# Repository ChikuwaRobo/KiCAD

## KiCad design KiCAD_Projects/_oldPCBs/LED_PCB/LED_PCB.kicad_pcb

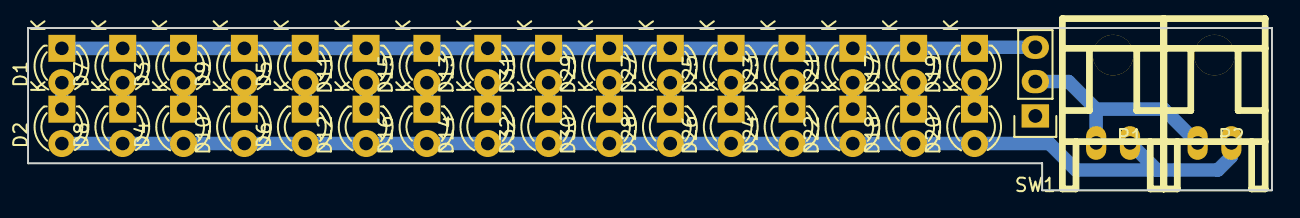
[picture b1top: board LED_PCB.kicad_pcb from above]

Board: 2 copper layers, 92.0 x 12.0 mm, 35 parts (0 on the bottom side), 19 nets.

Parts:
D1, D2, D3, D4, D5, D6, D7, D8, D9, D10, D11, D12, D13, D14, D15, D16, D17, D18, D19, D20, D21, D22, D23, D24, D25, D26, D27, D28, D29, D30, D31, D32: LED; LED-3MM
P1, P2: CONN_01X02; XA_2LC
SW1: SWITCH_INV; Pin_Header_Straight_1x03

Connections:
+BATT: P1.2, P2.2, SW1.2
GND: D2.2, D4.2, D6.2, D8.2, D10.2, D12.2, D14.2, D16.2, D18.2, D20.2, D22.2, D24.2, D26.2, D28.2, D30.2, D32.2, P1.1, P2.1
unnamed: D1.1, D3.1, D5.1, D7.1, D9.1, D11.1, D13.1, D15.1, D17.1, D19.1, D21.1, D23.1, D25.1, D27.1, D29.1, D31.1, SW1.3
unnamed: D1.2, D2.1
unnamed: D3.2, D4.1
unnamed: D5.2, D6.1
unnamed: D7.2, D8.1
unnamed: D9.2, D10.1
unnamed: D11.2, D12.1
unnamed: D13.2, D14.1
unnamed: D15.2, D16.1
unnamed: D17.2, D18.1
unnamed: D19.2, D20.1
unnamed: D21.2, D22.1
unnamed: D23.2, D24.1
unnamed: D25.2, D26.1
unnamed: D27.2, D28.1
unnamed: D29.2, D30.1
unnamed: D31.2, D32.1

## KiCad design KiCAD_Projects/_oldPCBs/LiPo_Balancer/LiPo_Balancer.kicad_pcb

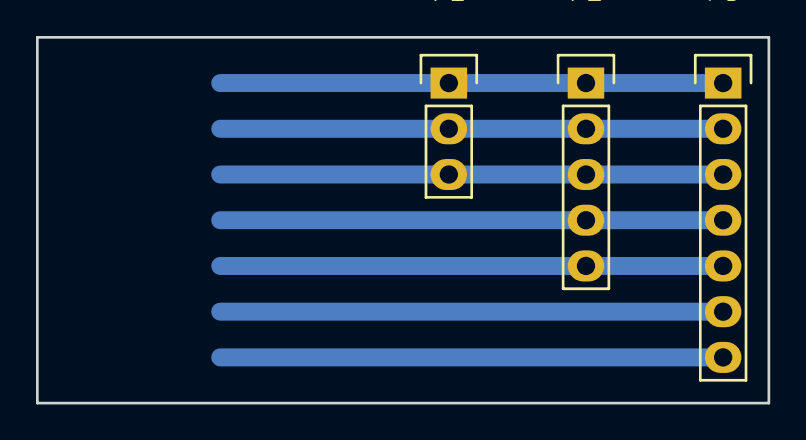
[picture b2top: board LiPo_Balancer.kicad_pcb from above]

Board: 2 copper layers, 40.6 x 20.3 mm, 3 parts (0 on the bottom side), 5 nets.

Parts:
P1: CONN_01X03; Pin_Header_Straight_1x03
P2: CONN_01X05; Pin_Header_Straight_1x05
P3: CONN_01X07; Pin_Header_Straight_1x07

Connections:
unnamed: P1.1, P2.1, P3.1
unnamed: P1.2, P2.2, P3.2
unnamed: P1.3, P2.3, P3.3
unnamed: P2.4, P3.4
unnamed: P2.5, P3.5

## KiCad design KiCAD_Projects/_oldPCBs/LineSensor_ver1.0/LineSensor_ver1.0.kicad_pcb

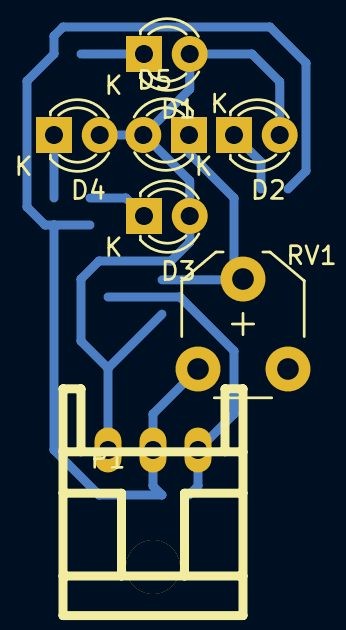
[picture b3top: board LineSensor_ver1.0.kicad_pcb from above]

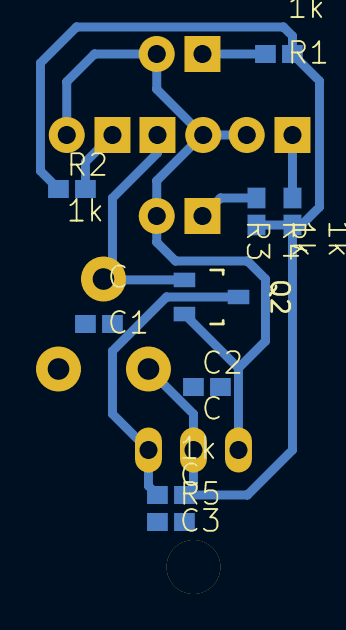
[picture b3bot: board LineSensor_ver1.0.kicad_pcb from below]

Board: 2 copper layers, 16 parts (9 on the bottom side), 8 nets.

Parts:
C1, C2, C3: C; C1608_NP
D1, D2, D3, D4, D5: LED; LED-3MM
P1: CONN_01X03; XA_3LC
Q2: MOSFET_N; SOT-23_Handsoldering
R1, R2, R3, R4, R5: 1k; C1608_NP
RV1: POT; Potentiometer_VishaySpectrol-Econtrim-Type36M

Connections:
+5V: C1.1, C2.1, C3.1, P1.2, R1.1, R2.1, R3.1, R4.1, R5.1, RV1.1
/SIGNAL: C3.2, P1.3, Q2.D, R5.2
GND: C2.2, D1.2, D2.2, D3.2, D4.2, D5.2, P1.1, Q2.S
unnamed: C1.2, D5.1, Q2.G, RV1.2
unnamed: D1.1, R1.2
unnamed: D2.1, R2.2
unnamed: D3.1, R3.2
unnamed: D4.1, R4.2

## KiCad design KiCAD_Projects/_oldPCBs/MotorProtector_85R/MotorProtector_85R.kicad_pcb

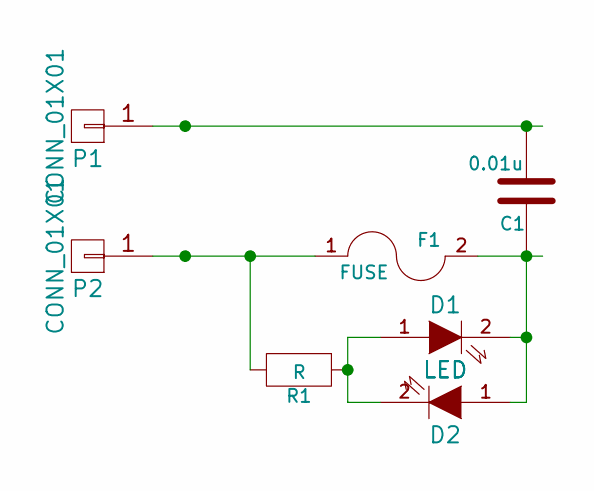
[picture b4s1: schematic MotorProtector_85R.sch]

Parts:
C1: 0.01u; C1608_WP
D1, D2: LED; C1608_WP
F1: FUSE; PolySwitch_W10P5
P1, P2: CONN_01X01; 1pin
R1: R; C1608_WP

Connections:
unnamed: C1.1, D1.2 (K), D2.1 (A), F1.2
unnamed: C1.2, P1.1
unnamed: D1.1 (A), D2.2 (K), R1.1
unnamed: F1.1, P2.1, R1.2

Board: 2 copper layers, 7 parts (4 on the bottom side), 4 nets, no tracks yet.

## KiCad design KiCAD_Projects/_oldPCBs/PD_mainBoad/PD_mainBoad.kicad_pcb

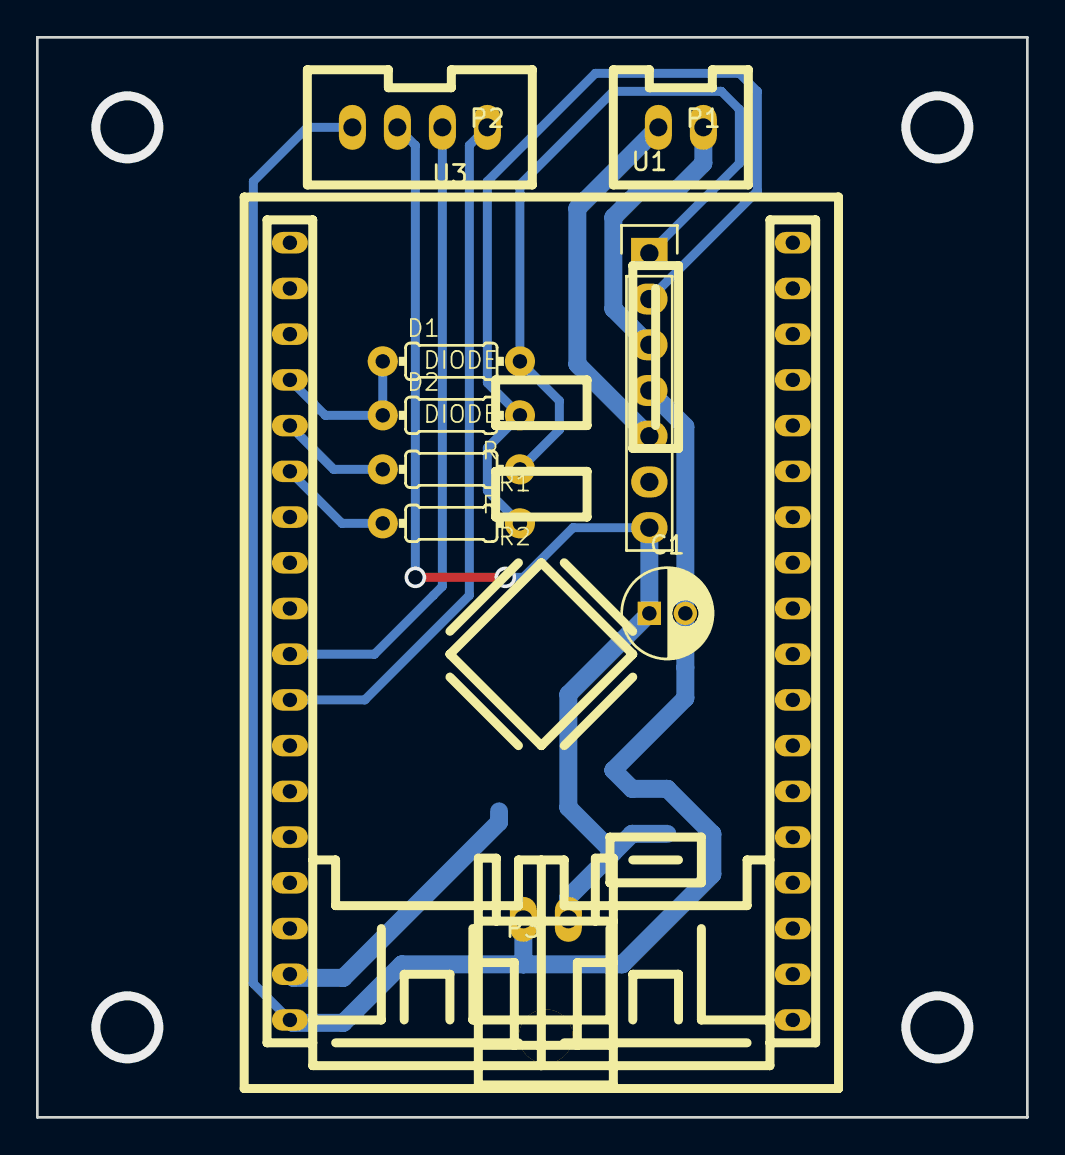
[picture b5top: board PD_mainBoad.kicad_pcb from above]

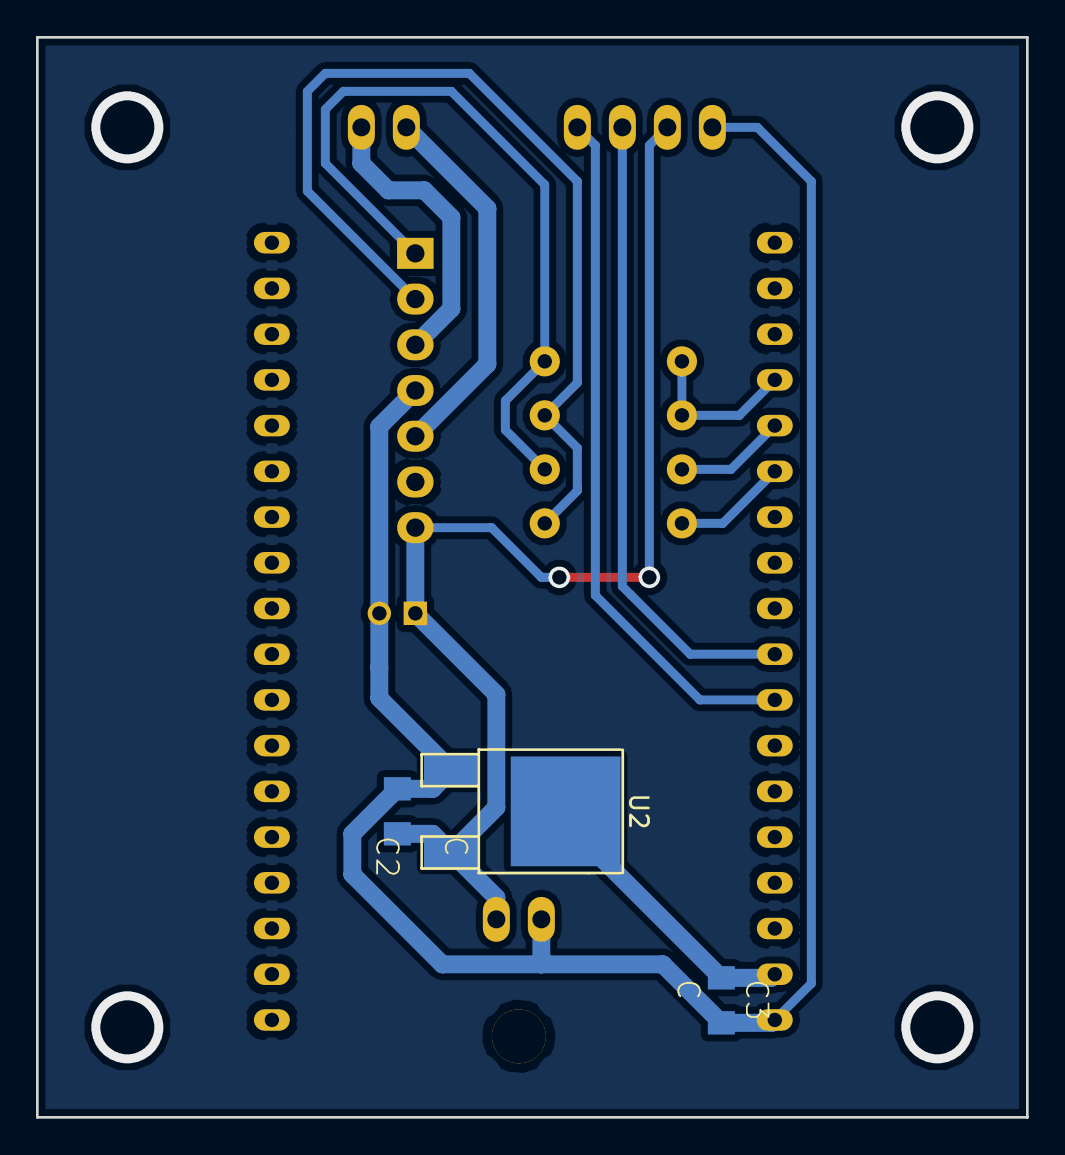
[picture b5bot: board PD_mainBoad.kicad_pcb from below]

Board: 2 copper layers, 55.0 x 60.0 mm, 13 parts (3 on the bottom side), 12 nets.

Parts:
C1: C; C_Radial_D5_L11_P2
C2, C3: C; C2012
D1, D2: DIODE; 0204_2f7
P1: CONN_01X02; XA_2T
P2: CONN_01X04; XA_4T
P3: CONN_01X02; XA_2LC
R1, R2: R; 0204_2f7
U1: TA8428K; Pin_Header_Straight_1x07
U2: NCP1117ST33T3G; TO-252-2Lead
U3: F103_mini

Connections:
+3.3V: C3.1, U2.2, U3.17
+BATT: C1.1, C2.1, P2.2, P3.2, U1.7, U2.3
/ENC_A: P2.3, U3.10
/ENC_B: P2.4, U3.11
/IN_A: R1.2, U3.5
/IN_B: R2.2, U3.6
/OUT_A: P1.2, U1.3
/OUT_B: P1.1, U1.5
/PWM: D1.1, D2.1, U3.4
GND: C1.2, C2.2, C3.2, P2.1, P3.1, U1.4, U2.1, U3.18
unnamed: D1.2, R1.1, U1.1
unnamed: D2.2, R2.1, U1.2

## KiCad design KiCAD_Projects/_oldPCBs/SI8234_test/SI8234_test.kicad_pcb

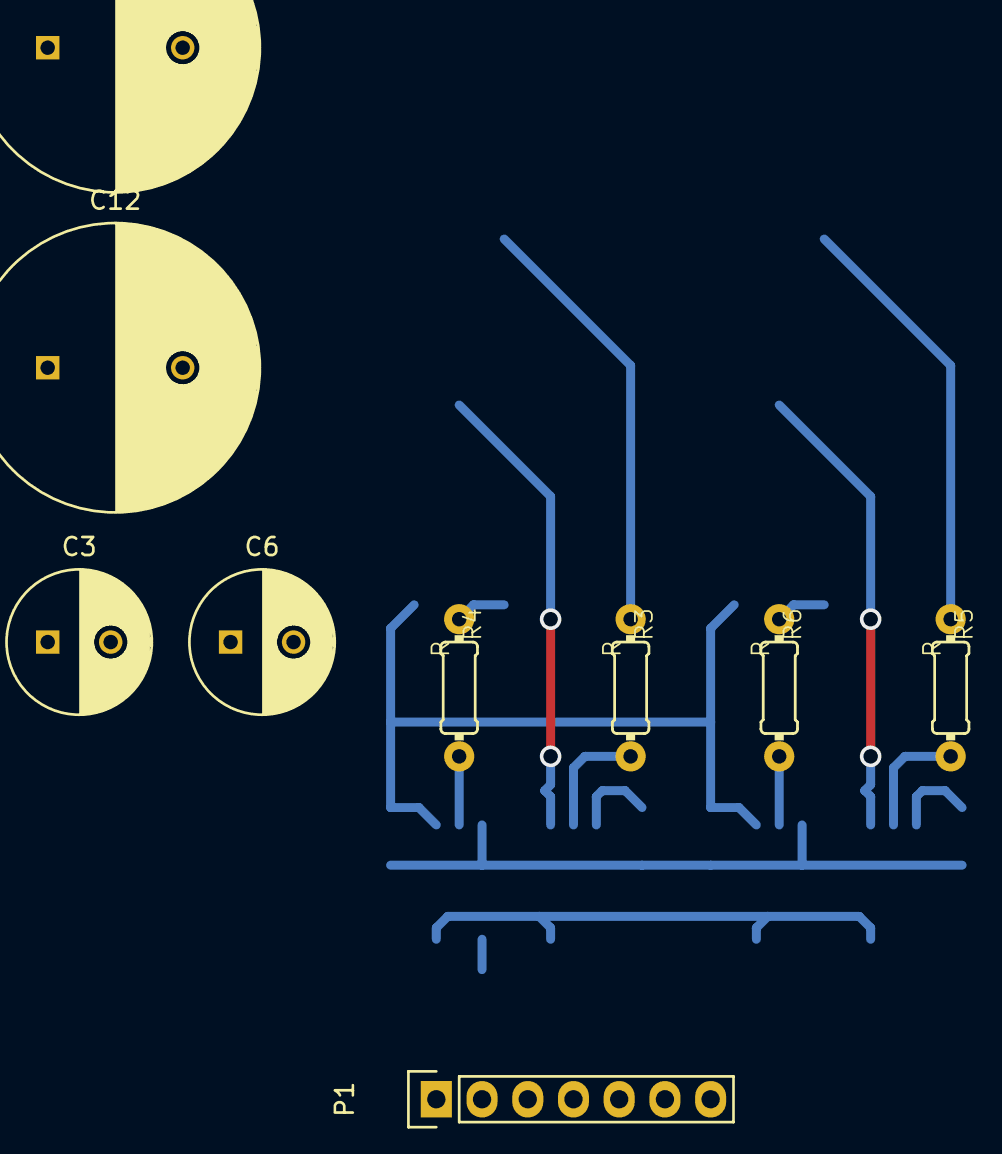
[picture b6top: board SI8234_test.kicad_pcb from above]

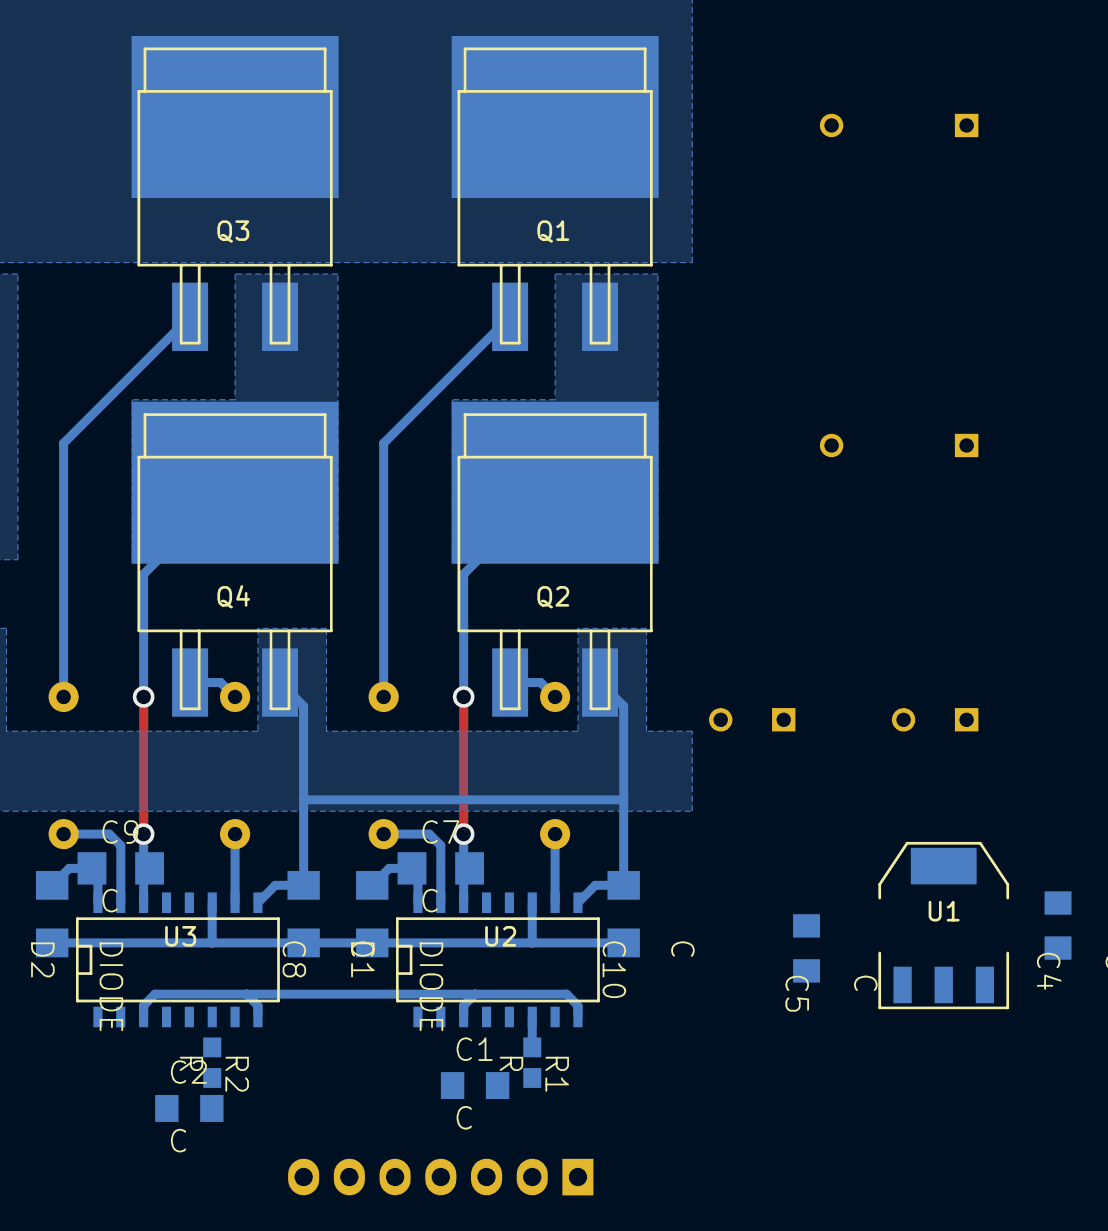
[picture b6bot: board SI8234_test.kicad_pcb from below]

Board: 2 copper layers, 28 parts (19 on the bottom side), 20 nets.

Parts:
C1, C2, C4, C5: C; C2012
C3, C6: C; C_Radial_D8_L11.5_P3.5
C7, C8, C9, C10: C; C3216
C12, C13: C; C_Radial_D16_L30_P7.5
D1, D2: DIODE; C3216
P1: CONN_01X07; Pin_Header_Straight_1x07
Q1, Q2, Q3, Q4: MOSFET_N; D2-PAK
R1, R2: R; C1608
R3, R4, R5, R6: R; 0204_2f7
U1: NCP1117ST12T3G; SOT-223
U2, U3: SI8234; SO-16-N

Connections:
+5V: C1.1, C2.1, P1.2, U2.3, U2.8, U3.3, U3.8
+BATT: C3.1, C4.1, C12.1, C13.1, Q1.D, Q3.D, U1.3
/GD_PS: C5.1, C6.1, C8.1, C10.1, D1.1, D2.1, U1.2, U2.11, U3.11
/~EN: P1.5, U2.5, U3.5
GND: C1.2, C2.2, P1.3, R1.2, R2.2, U2.4, U3.4
GNDPWR: C3.2, C4.2, C5.2, C6.2, C8.2, C10.2, C12.2, C13.2, Q2.S, Q4.S, U1.1, U2.9, U3.9
unnamed: C7.1, D1.2, U2.16
unnamed: C7.2, Q1.S, Q2.D, U2.14
unnamed: C9.1, D2.2, U3.16
unnamed: C9.2, Q3.S, Q4.D, U3.14
unnamed: Q1.G, R3.1
unnamed: Q2.G, R4.1
unnamed: Q3.G, R5.1
unnamed: Q4.G, R6.1
unnamed: R1.1, U2.6
unnamed: R2.1, U3.6
unnamed: R3.2, U2.15
unnamed: R4.2, U2.10
unnamed: R5.2, U3.15
unnamed: R6.2, U3.10

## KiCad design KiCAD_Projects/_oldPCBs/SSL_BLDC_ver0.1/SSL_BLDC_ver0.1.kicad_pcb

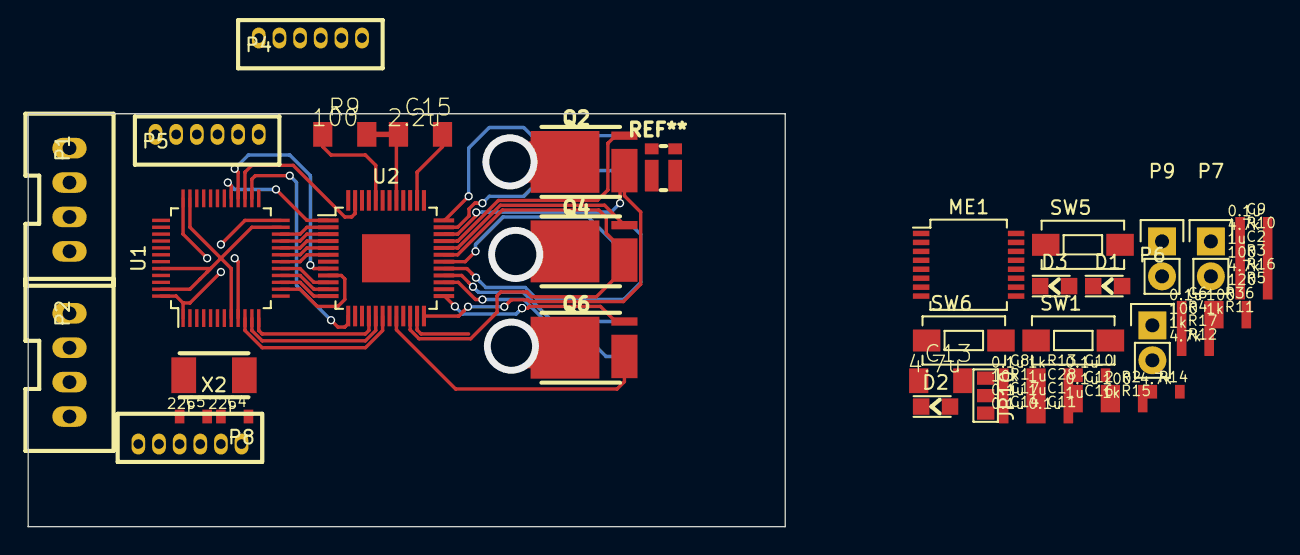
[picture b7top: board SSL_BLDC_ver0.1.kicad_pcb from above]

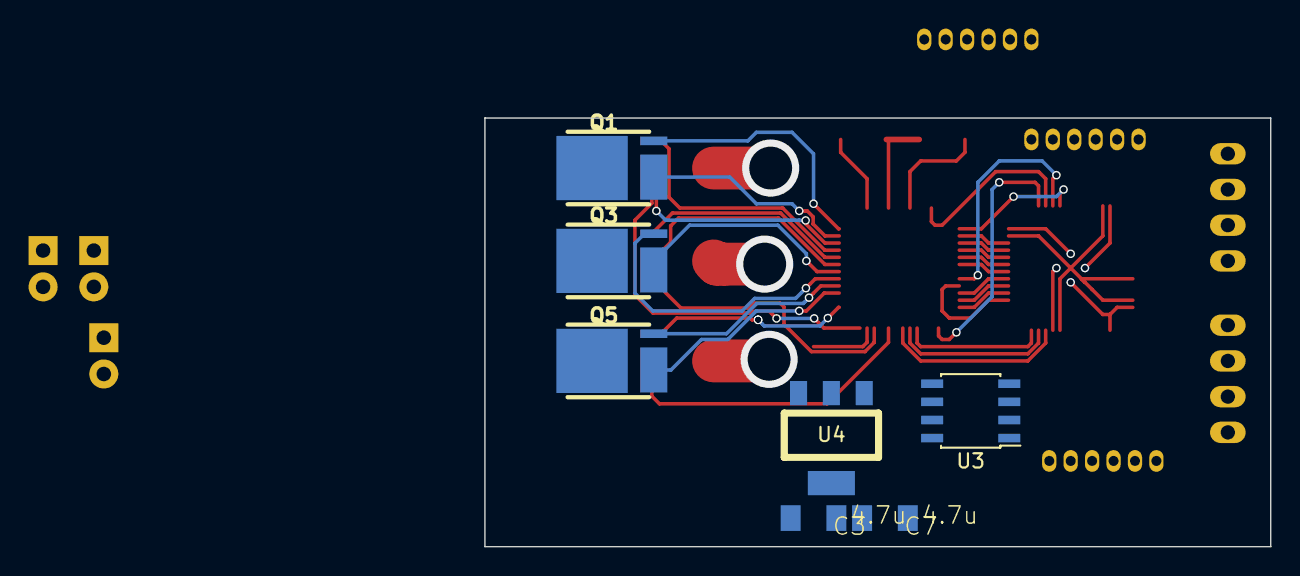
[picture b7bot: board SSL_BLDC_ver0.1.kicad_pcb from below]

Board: 2 copper layers, 55.0 x 30.0 mm, 60 parts (7 on the bottom side), 77 nets.

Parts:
C1, C2, C16, C28: 1u; C1608_WP_S
C3, C7, C13: 4.7u; C3216_S
C4, C5: 22p; C1608_WP_S
C6, C8, C9, C10, C11, C12, C14, C17: 0.1u; C1608_WP_S
C15: 2.2u; C3216_S
D1, D2, D3: LED; LED_0805
JP10: JUMPER3; GS3
ME1: AS504x; SSOP-16_5.3x6.2mm_Pitch0.65mm
P1, P2: CONN_01X04; XA_4T
P4, P5, P8: CONN_01X06; ZH_6T
P6, P7, P9: CONN_01X02; Pin_Header_Straight_1x02
Q1, Q2, Q3, Q4, Q5, Q6: MOSFET_N; DFN56
R1: 10k; C1608_WP_S
R2, R3, R4, R36: 100; C1608_WP_S
R5: 120; C1608_WP_S
R9: 100; C3216_S
R10, R12, R14, R16: 4.7k; C1608_WP_S
R11, R13, R15, R17: 1k; C1608_WP_S
SW1, SW5, SW6: SW_PUSH; SW_SPST_EVQPE1
U1: STM32F103_48; LQFP-48_7x7mm_Pitch0.5mm
U2: DRV8305; TQFP-48-1EP_7x7mm_Pitch0.5mm
U3: MAX3051; SOIC-8_3.9x4.9mm_Pitch1.27mm
U4: NCP1117ST50T3G; SOT-223_reg
X2: CRYSTAL; ABM3_2pads

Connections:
+3.3V: C3.1, C6.2, C8.2, C9.2, C10.2, C11.2, D1.1, JP10.3, P4.2, R1.1, U1.1, U1.9, U1.24, U1.36, U1.48, U3.3, U4.2
+5V: C7.1, P1.2, P2.2, U4.3
+BATT: C13.2, C15.1, Q1.D, Q3.D, Q5.D, R9.2, R16.1, U2.41
/AS_3.3V: C17.2, ME1.15, ME1.16, P8.2
/AS_ENC_A: ME1.3, P9.1
/AS_ENC_B: ME1.4, P9.2
/AS_GND: C17.1, ME1.7, P8.1
/AS_SPI_MISO: ME1.9, P8.5
/AS_SPI_NSS_ENC: ME1.11, P8.3
/AS_SPI_SCK: ME1.10, P8.4
/BATT_V: R16.2, R17.1, U1.13
/CAN_H: P1.3, P2.3, P6.1, U3.7
/CAN_L: P1.4, P2.4, R5.1, U3.6
/CAN_RX: U1.32, U3.4
/CAN_TX: U1.33, U3.1
/CS_U: U1.12, U2.16
/CS_V: U1.11, U2.17
/CS_W: U1.10, U2.18
/ENC_A: P7.1, U1.42
/ENC_B: P7.2, U1.43
/GATE_U_H: Q1.G, U2.36
/GATE_U_L: Q2.G, U2.33
/GATE_V_H: Q3.G, U2.29
/GATE_V_L: Q4.G, U2.32
/GATE_W_H: Q5.G, U2.28
/GATE_W_L: Q6.G, U2.25
/GD_EN: U1.29, U2.1
/GD_WAKE: U1.27, U2.47
/IN_DWL: U1.18, U2.6
/IN_S0: U1.21, U2.3
/IN_S1: U1.20, U2.4
/IN_S2: U1.19, U2.5
/LED_A: D2.1, U1.3
/LED_B: D3.1, U1.4
/NRST: R1.2, SW1.2, U1.7
/OSC_IN: C4.1, U1.5, X2.1
/OSC_OUT: C5.1, U1.6, X2.2
/OUT_U: Q1.S, Q2.D, R10.1, U2.35
/OUT_V: Q3.S, Q4.D, R12.1, U2.30
/OUT_W: Q5.S, Q6.D, R14.1, U2.27
/PWGD: U1.26, U2.13
/PWM: U1.22, U2.2
/SPI_MISO: P4.5, U1.16, U2.11
/SPI_MOSI: P4.6, U1.17, U2.10
/SPI_NSS_ENC: P4.3, U1.25
/SPI_NSS_GD: U1.14, U2.9
/SPI_SCK: P4.4, U1.15, U2.12
/SWCLK: P5.3, U1.37
/SWDIO: P5.4, U1.34
/S_U_L: Q2.S, U2.24, U2.34
/S_V_L: Q4.S, U2.22, U2.31
/S_W_L: Q6.S, U2.20, U2.26
/USART_RX: P5.6, U1.31
/USART_TX: P5.5, U1.30
/VS_U: R10.2, R11.1
/VS_V: R12.2, R13.1
/VS_W: R14.2, R15.1
/nFALUT: U1.28, U2.8
GND: C1.1, C2.1, C3.2, C4.2, C5.2, C6.1, C7.2, C8.1, C9.1, C10.1, C11.1, C13.1, C16.1, C28.1, P1.1, P2.1, P4.1, P5.1, R2.2, R3.2, R4.2, R36.2, SW1.1, SW5.2, SW6.2, U1.8, U1.23, U1.35, U1.44, U1.47, U2.14, U2.45, U2.49, U3.2, U3.5, U3.8, U4.1
GNDPWR: R11.2, R13.2, R15.2, R17.2, R36.1, U2.19, U2.21, U2.23
unnamed: C1.2, U2.46
unnamed: C2.2, U2.15
unnamed: C12.1, U2.43
unnamed: C12.2, U2.42
unnamed: C14.1, U2.40
unnamed: C14.2, U2.39
unnamed: C15.2, U2.38
unnamed: C16.2, U2.37
unnamed: C28.2, U2.48
unnamed: D1.2, R3.1
unnamed: D2.2, R4.1
unnamed: D3.2, R2.1
unnamed: JP10.2, P5.2
unnamed: P6.2, R5.2
unnamed: R9.1, U2.44
unnamed: SW5.1, U1.39
unnamed: SW6.1, U1.38
